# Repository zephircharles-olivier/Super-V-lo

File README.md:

C’est en combinant passion pour le cyclisme et intérêt pour les systèmes embarqués que j’ai imaginé le Super Vélo : un projet de fin d’année visant à transformer un vélo traditionnel en un moyen de transport intelligent, pratique et connecté.

Le Super Vélo, comme son nom l’indique, regroupe une série d’améliorations techniques soigneusement intégrées. Éclairage avant, feux de signalisation, et collecte de données en temps réel ne sont que quelques-unes des fonctionnalités que j’ai développées pour améliorer la sécurité et l’expérience utilisateur. Grâce à une connexion Internet, les données de vitesse et de fréquence cardiaque sont transmises sur une base de données et consultables directement sur un téléphone cellulaire.

Vous pouvez trouvez içi le code source, les schémas électroniques, les fichiers Gerbers et les fichiers de conception

Voir le projet sur mon site Web: https://tgemaisonneuve.com/wp-admin/post.php?post=1706&action=edit

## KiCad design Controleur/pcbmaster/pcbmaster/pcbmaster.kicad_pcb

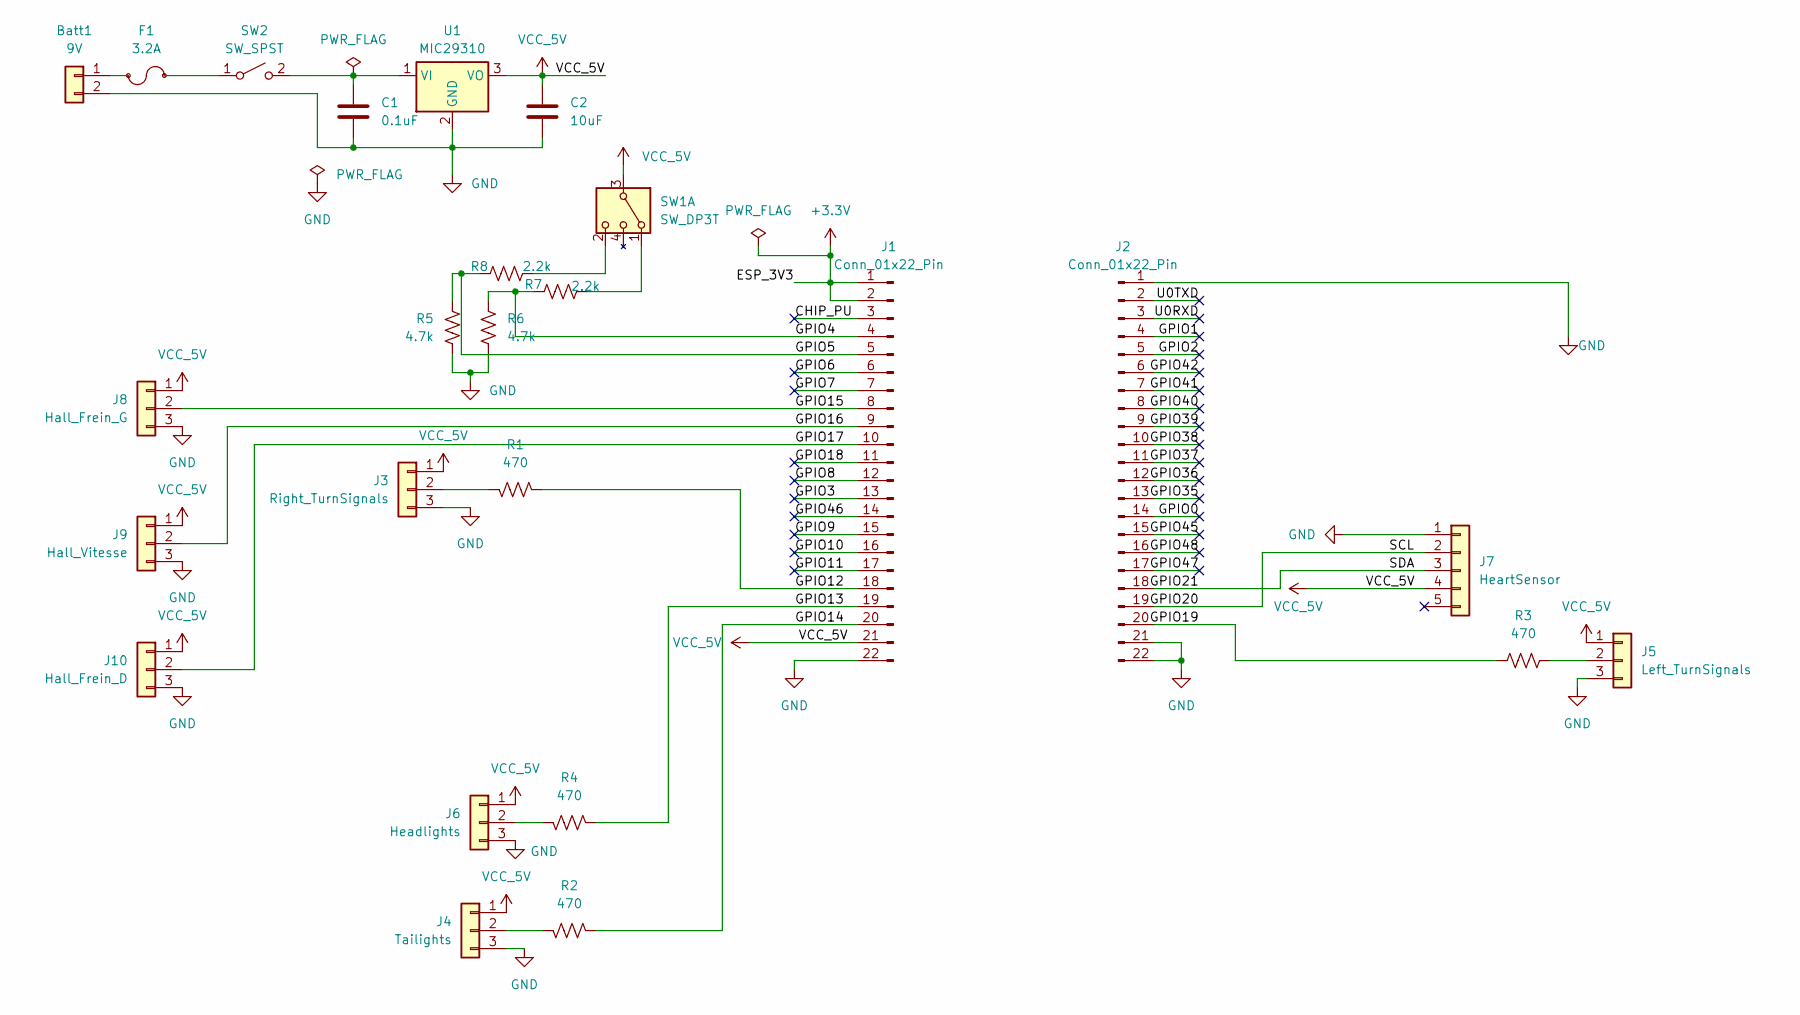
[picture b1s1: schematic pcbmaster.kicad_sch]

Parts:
Batt1: 9V; 691137710002
C1: 0.1uF; C_0805_2012Metric_Pad1.18x1.45mm_HandSolder
C2: 10uF; C_0805_2012Metric_Pad1.18x1.45mm_HandSolder
F1: 3.2A; FUSE_3519
J1, J2: Conn_01x22_Pin; PinHeader_1x22_P2.54mm_Vertical
J3: Right_TurnSignals; CONN_3pos_GREEN
J4: Tailights; CONN_3pos_GREEN
J5: Left_TurnSignals; CONN_3pos_GREEN
J6: Headlights; CONN_3pos_GREEN
J7: HeartSensor; CONN_5_pos_GREEN
J8: Hall_Frein_G; CONN_3pos_GREEN
J9: Hall_Vitesse; CONN_3pos_GREEN
J10: Hall_Frein_D; CONN_3pos_GREEN
R1, R2, R3, R4: 470; R_0805_2012Metric_Pad1.20x1.40mm_HandSolder
R5, R6: 4.7k; LED_0805_2012Metric_Pad1.15x1.40mm_HandSolder
R7, R8: 2.2k; LED_0805_2012Metric_Pad1.15x1.40mm_HandSolder
SW1: SW_DP3T; CONN_3pos_GREEN
SW2: SW_SPST; 691137710002
U1: MIC29310; TO-220-3_MCL

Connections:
+3.3V: J1.1, J1.2
/CHIP_PU: J1.3
/GPIO0: J2.14
/GPIO1: J2.4
/GPIO2: J2.5
/GPIO3: J1.13
/GPIO4: J1.4, R6.2, R7.1, R7.2, SW1.1 (IO1)
/GPIO5: J1.5, R5.2, R8.1, R8.2, SW1.2 (IO2)
/GPIO6: J1.6
/GPIO7: J1.7
/GPIO8: J1.12
/GPIO9: J1.15
/GPIO10: J1.16
/GPIO11: J1.17
/GPIO12: J1.18, R1.1
/GPIO13: J1.19, R4.1
/GPIO14: J1.20, R2.1
/GPIO15: J1.8, J8.2
/GPIO16: J1.9, J9.2
/GPIO17: J1.10, J10.2
/GPIO18: J1.11
/GPIO19: J2.20, R3.1
/GPIO20: J2.19, J7.2
/GPIO21: J2.18, J7.3
/GPIO35: J2.13
/GPIO36: J2.12
/GPIO37: J2.11
/GPIO38: J2.10
/GPIO39: J2.9
/GPIO40: J2.8
/GPIO41: J2.7
/GPIO42: J2.6
/GPIO45: J2.15
/GPIO46: J1.14
/GPIO47: J2.17
/GPIO48: J2.16
/U0RXD: J2.3
/U0TXD: J2.2
GND: Batt1.2, C1.2, C2.2, J1.22, J2.1, J2.21, J2.22, J3.3, J4.3, J5.3, J6.3, J7.1, J8.3, J9.3, J10.3, R5.1, R6.1, U1.2 (GND)
unnamed: Batt1.1, F1.1
unnamed: J3.2, R1.2
unnamed: J4.2, R2.2
unnamed: J5.2, R3.2
unnamed: J6.2, R4.2
unnamed: F1.2, SW2.1 (A)
unnamed: C1.1, SW2.2 (B), U1.1 (VI)
VCC_5V: C2.1, J1.21, J3.1, J4.1, J5.1, J6.1, J7.4, J8.1, J9.1, J10.1, SW1.3 (VCC), U1.3 (VO)

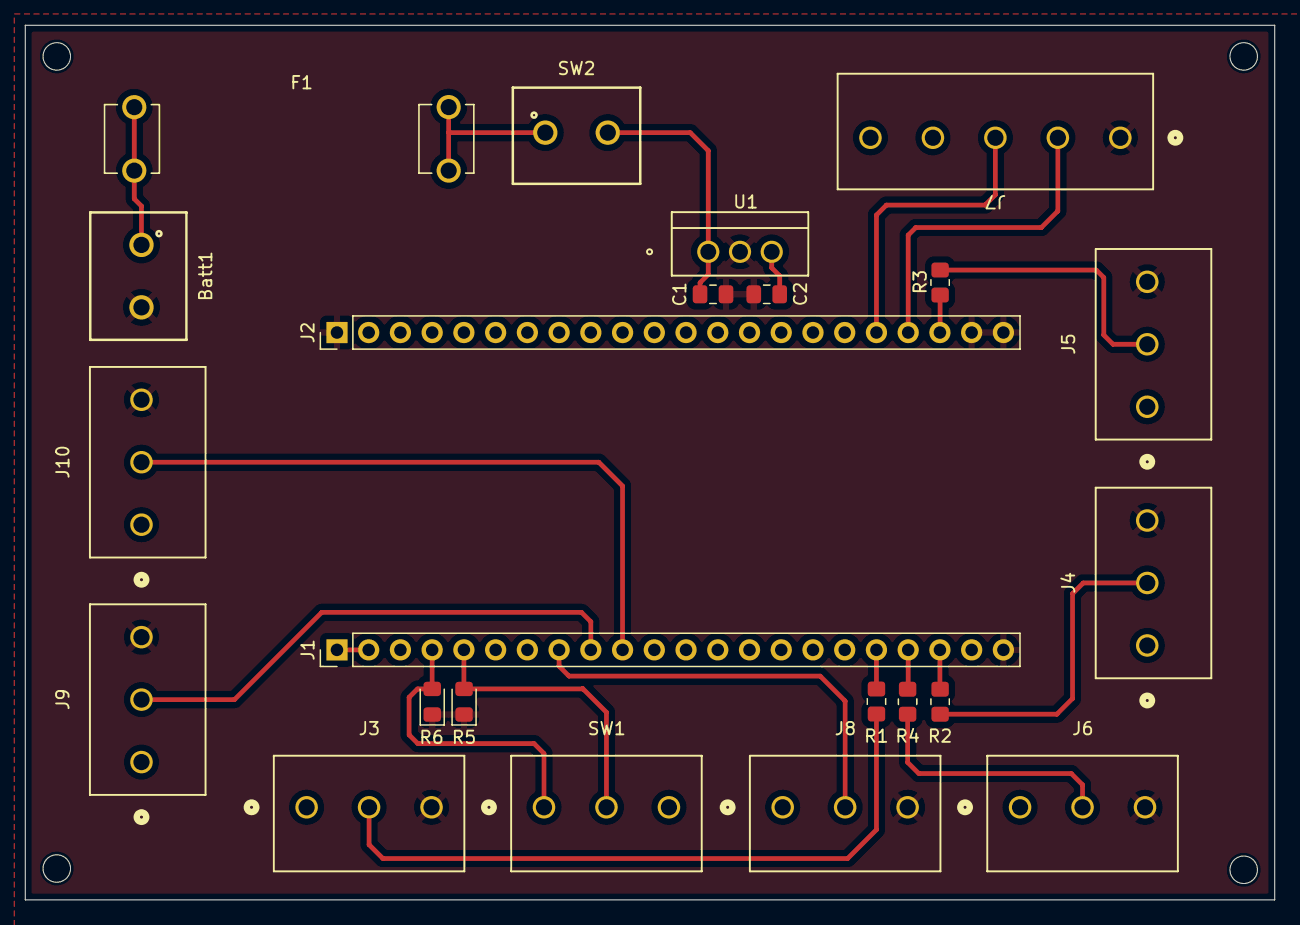
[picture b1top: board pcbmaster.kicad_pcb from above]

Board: 2 copper layers, 100.0 x 70.0 mm, 23 parts (0 on the bottom side), 21 nets.

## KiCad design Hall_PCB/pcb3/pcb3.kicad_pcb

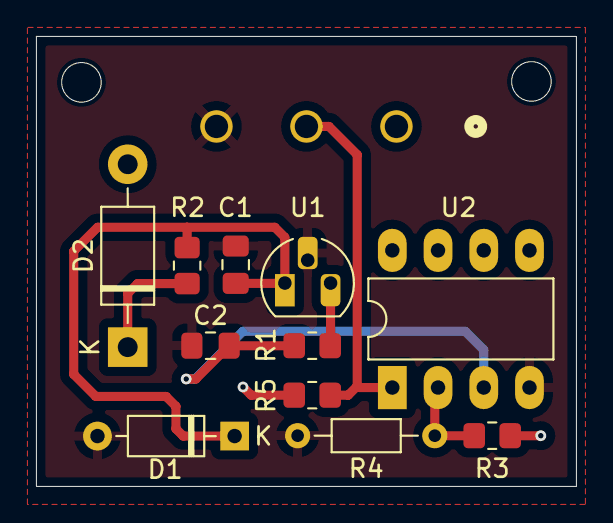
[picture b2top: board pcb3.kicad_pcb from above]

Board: 2 copper layers, 30.0 x 25.0 mm, 12 parts (1 on the bottom side), 8 nets.

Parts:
C1: 100nF; C_0805_2012Metric_Pad1.18x1.45mm_HandSolder
C2: 4.7nF; C_0805_2012Metric_Pad1.18x1.45mm_HandSolder
D1: D_Zener; D_DO-35_SOD27_P7.62mm_Horizontal
D2: 1N4004-TP; D_DO-41_SOD81_P10.16mm_Horizontal
J1: Hall_Vitesse; CONN_3pos_GREEN
R1, R3, R5: 10k; R_0805_2012Metric_Pad1.20x1.40mm_HandSolder
R2: 100; R_0805_2012Metric_Pad1.20x1.40mm_HandSolder
R4: 500; R_Axial_DIN0204_L3.6mm_D1.6mm_P7.62mm_Horizontal
U1: US5881; TO-92L_HandSolder
U2: LM393; DIP-8_W7.62mm_LongPads

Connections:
+5V: D2.2 (A), J1.1, R3.1, R5.1, U2.8 (V+)
/OUT_5V: J1.2, R5.2, U2.1
GND: C1.2, C2.1, D1.2 (A), J1.3, R4.2, U1.2 (GND), U2.4 (V-)
unnamed: C1.1, D1.1 (K), R2.2, U1.1 (VDD)
unnamed: D2.1 (K), R2.1
unnamed: R1.1, U1.3 (OUT)
unnamed: C2.2, R1.2, U2.3 (+)
unnamed: R3.2, R4.1, U2.2 (-)

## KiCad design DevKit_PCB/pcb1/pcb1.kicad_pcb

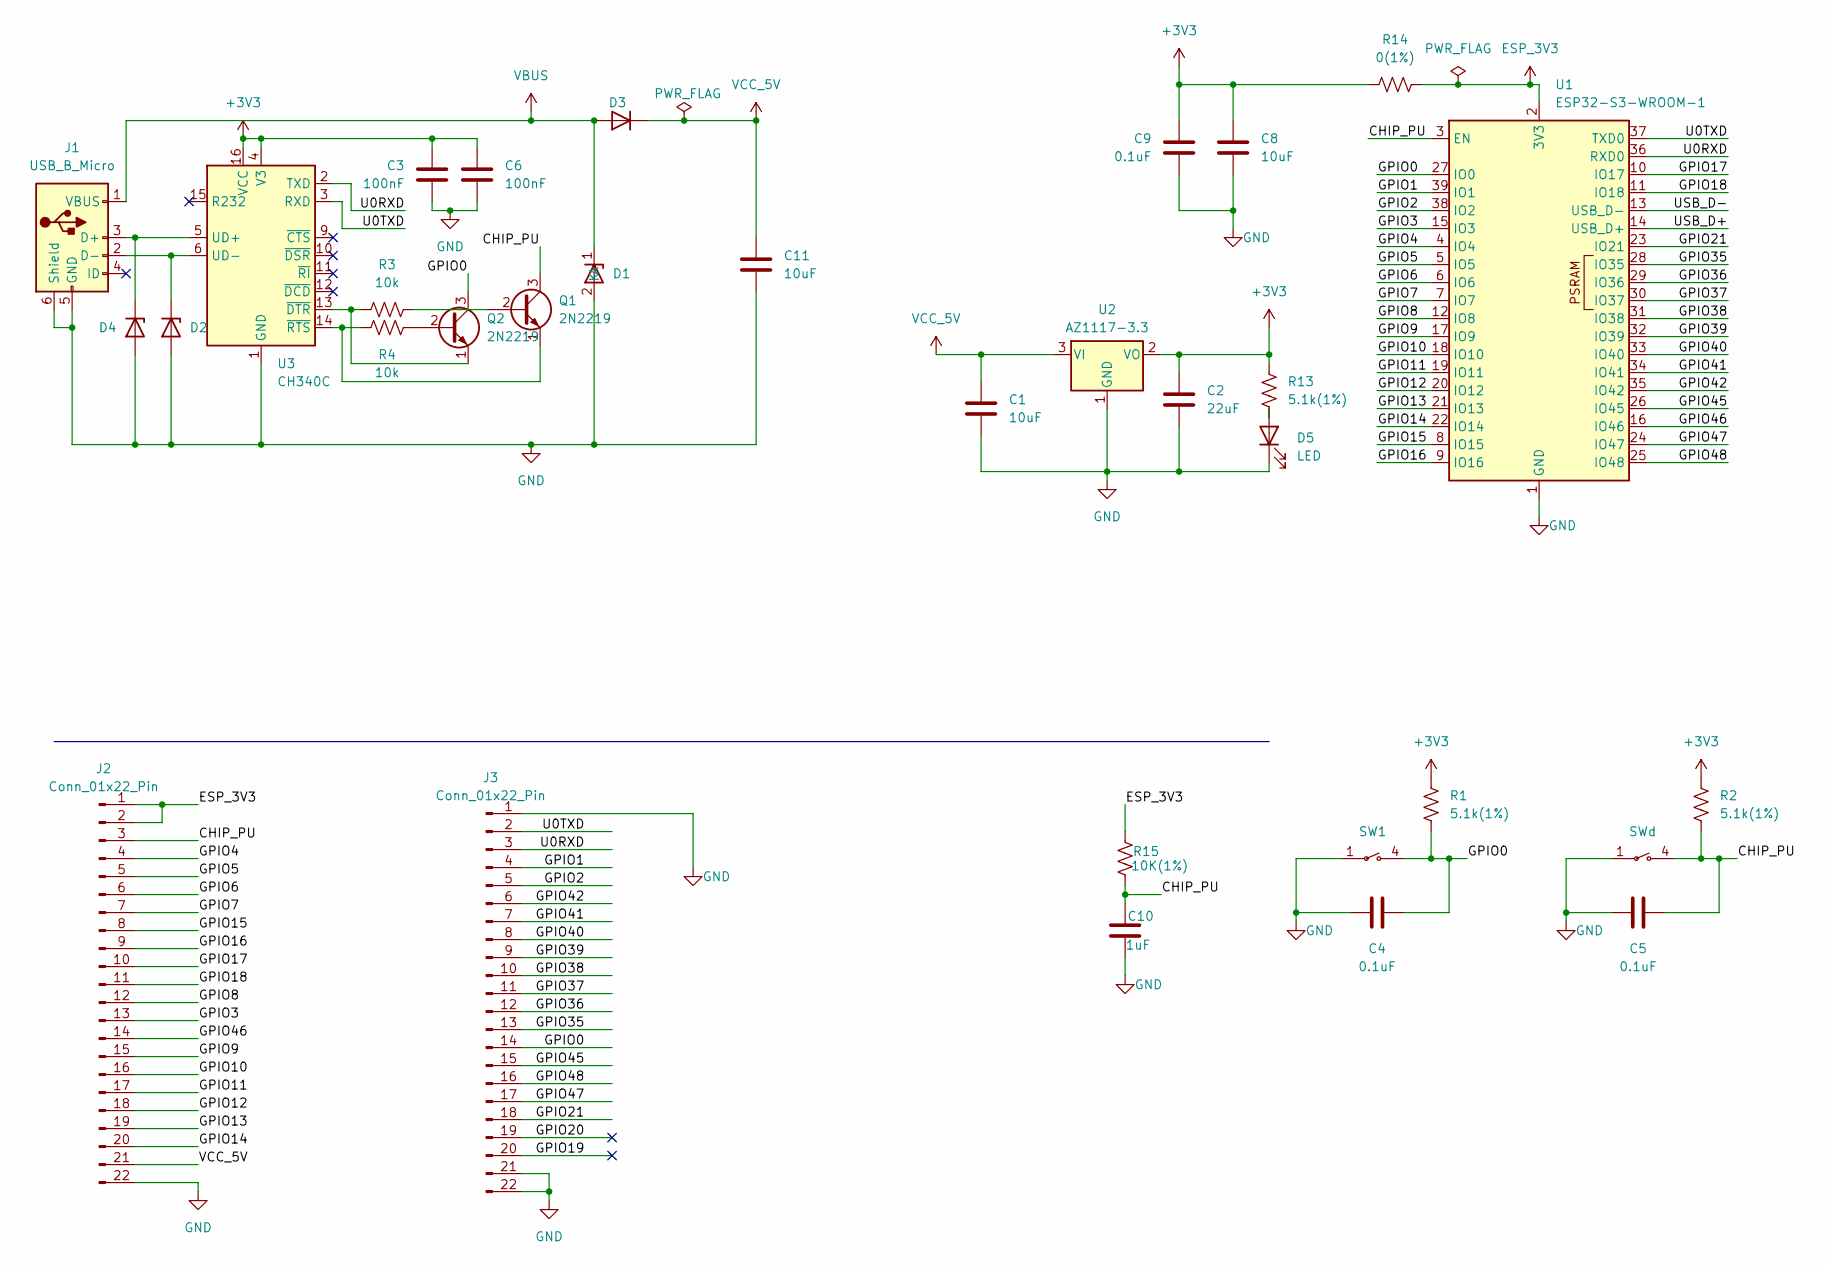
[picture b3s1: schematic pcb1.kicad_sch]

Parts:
C1, C11: 10uF; C_10uF
C2: 22uF; C_size0805
C3, C6: 100nF; C_size0805
C4, C5, C9: 0.1uF; C_0805_2012Metric
C8: 10uF; C_size0805
C10: 1uF; C_0805_2012Metric
D1, D2, D4: SMA6J58CA-Q; CR_041-1JY_STM
D3: Schottky
D5: LED; LED_R
J1: USB_B_Micro; USB2.0(10118193)
J2, J3: Conn_01x22_Pin; PinHeader_1x22_P2.54mm_Vertical
Q1, Q2: 2N2219; BSR14
R1, R2, R13: 5.1k(1%); R_0805_2012Metric
R3, R4: 10k; R_10k(1%)
R14: 0(1%); R_0
R15: 10K(1%); R_10k(1%)
SW1: PTS 647 SN50 SMTR2 LFS
SWd: PTS 647 SN50 SMTR2 LFS
U1: ESP32-S3-WROOM-1
U2: AZ1117-3.3; SOT-223-3_TabPin2
U3: CH340C; SOIC-16_3.9x9.9mm_P1.27mm

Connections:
+3V3: C2.1, C3.1, C6.1, C8.1, C9.1, R1.2, R2.2, R13.2, R14.1, U2.2 (VO), U3.4 (V3), U3.16 (VCC)
/CHIP_PU: C5.2, C10.1, J2.3, Q1.3 (C), R2.1, R15.2, SWd.4, U1.3 (EN); also elsewhere on the board
/GPIO0: C4.2, J3.14, Q2.3 (C), R1.1, SW1.4, U1.27 (IO0)
/GPIO1: J3.4, U1.39 (IO1)
/GPIO2: J3.5, U1.38 (IO2)
/GPIO3: J2.13, U1.15 (IO3)
/GPIO4: J2.4, U1.4 (IO4)
/GPIO5: J2.5, U1.5 (IO5)
/GPIO6: J2.6, U1.6 (IO6)
/GPIO7: J2.7, U1.7 (IO7)
/GPIO8: J2.12, U1.12 (IO8)
/GPIO9: J2.15, U1.17 (IO9)
/GPIO10: J2.16, U1.18 (IO10)
/GPIO11: J2.17, U1.19 (IO11)
/GPIO12: J2.18, U1.20 (IO12)
/GPIO13: J2.19, U1.21 (IO13)
/GPIO14: J2.20, U1.22 (IO14)
/GPIO15: J2.8, U1.8 (IO15)
/GPIO16: J2.9, U1.9 (IO16)
/GPIO17: J2.10, U1.10 (IO17)
/GPIO18: J2.11, U1.11 (IO18)
/GPIO19: J3.20
/GPIO20: J3.19
/GPIO21: J3.18, U1.23 (IO21)
/GPIO35: J3.13, U1.28 (IO35)
/GPIO36: J3.12, U1.29 (IO36)
/GPIO37: J3.11, U1.30 (IO37)
/GPIO38: J3.10, U1.31 (IO38)
/GPIO39: J3.9, U1.32 (IO39)
/GPIO40: J3.8, U1.33 (IO40)
/GPIO41: J3.7, U1.34 (IO41)
/GPIO42: J3.6, U1.35 (IO42)
/GPIO45: J3.15, U1.26 (IO45)
/GPIO46: J2.14, U1.16 (IO46)
/GPIO47: J3.17, U1.24 (IO47)
/GPIO48: J3.16, U1.25 (IO48)
/U0RXD: J3.3, U1.36 (RXD0), U3.2 (TXD)
/U0TXD: J3.2, U1.37 (TXD0), U3.3 (RXD)
/USB_D+: U1.14 (USB_D+)
/USB_D-: U1.13 (USB_D-)
ESP_3V3: J2.1, J2.2, R14.2, R15.1, U1.2 (3V3)
GND: C1.2, C2.2, C3.2, C4.1, C5.1, C6.2, C8.2, C9.2, C10.2, C11.2, D1.2 (A), D2.2 (A), D4.2 (A), D5.1 (K), J1.5 (GND), J1.6 (Shield), J2.22, J3.1, J3.21, J3.22, SW1.1, SWd.1, U1.1 (GND), U1.40 (GND), U1.41 (GND), U2.1 (GND), U3.1 (GND); also elsewhere on the board
unnamed: D2.1 (K), J1.2 (D-), U3.6 (UD-)
unnamed: D4.1 (K), J1.3 (D+), U3.5 (UD+)
unnamed: D5.2 (A), R13.1
unnamed: Q1.2 (B), R3.2
unnamed: Q1.1 (E), R4.1, U3.14 (~RTS)
unnamed: Q2.2 (B), R4.2
unnamed: Q2.1 (E), R3.1, U3.13 (~DTR)
VBUS: D1.1 (K), D3.2 (A), J1.1 (VBUS)
VCC_5V: C1.1, C11.1, D3.1 (K), J2.21, U2.3 (VI)

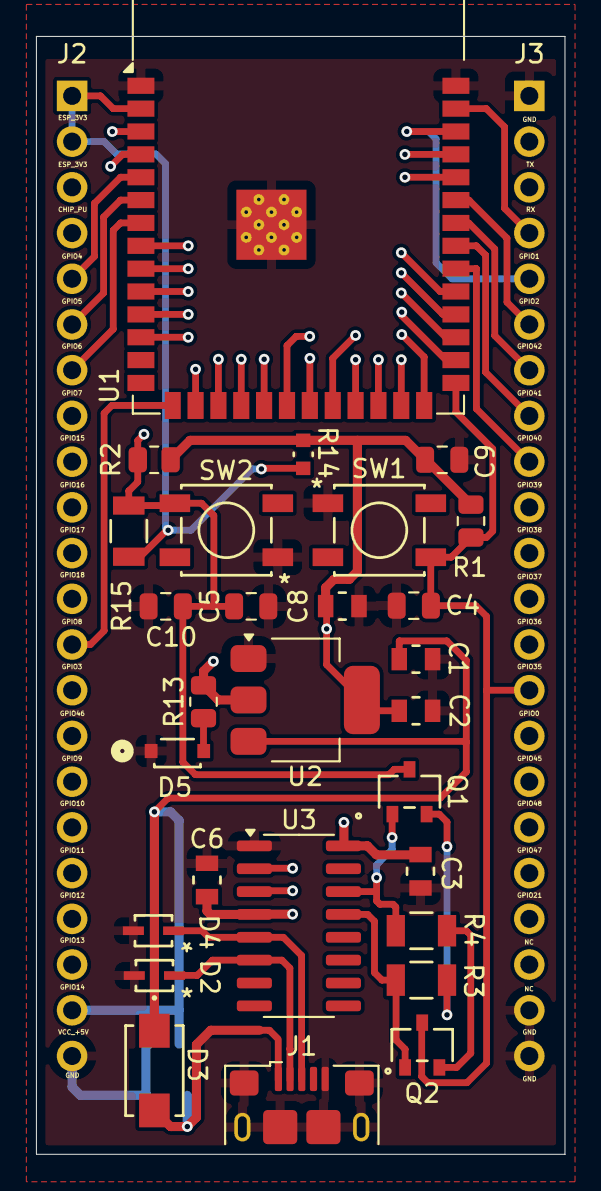
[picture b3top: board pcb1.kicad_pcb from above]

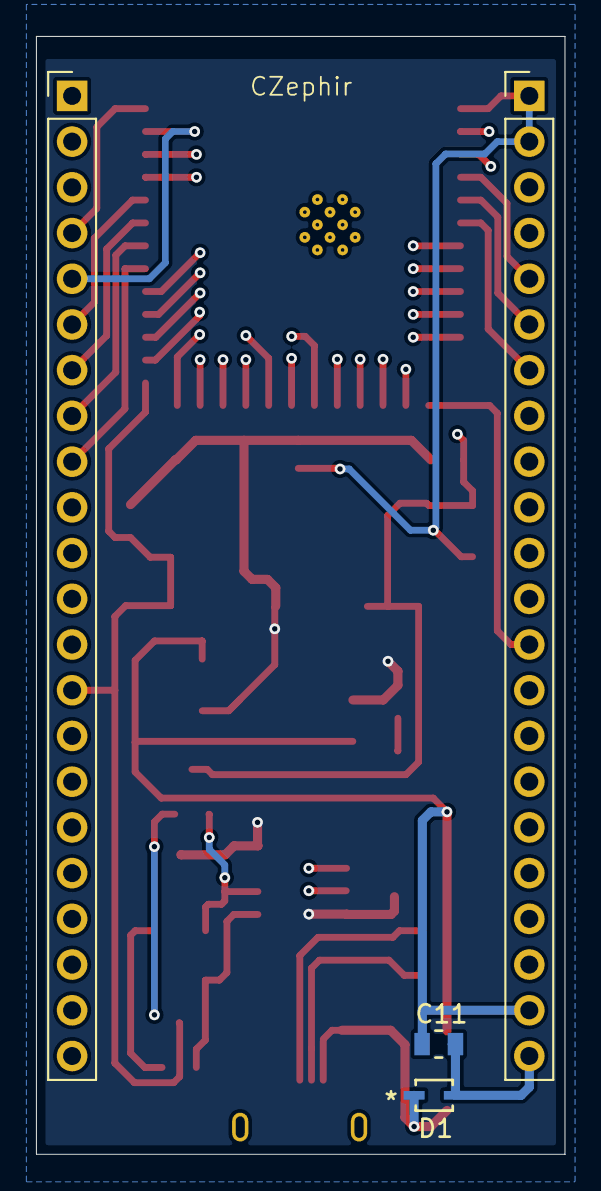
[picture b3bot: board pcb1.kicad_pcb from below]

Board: 4 copper layers, 29.4 x 62.1 mm, 32 parts (4 on the bottom side), 47 nets.

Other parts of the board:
SW2: PTS 647 SN50 SMTR2 LFS

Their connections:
/CHIP_PU: SW2.4; also elsewhere on the board
GND: SW2.1; also elsewhere on the board

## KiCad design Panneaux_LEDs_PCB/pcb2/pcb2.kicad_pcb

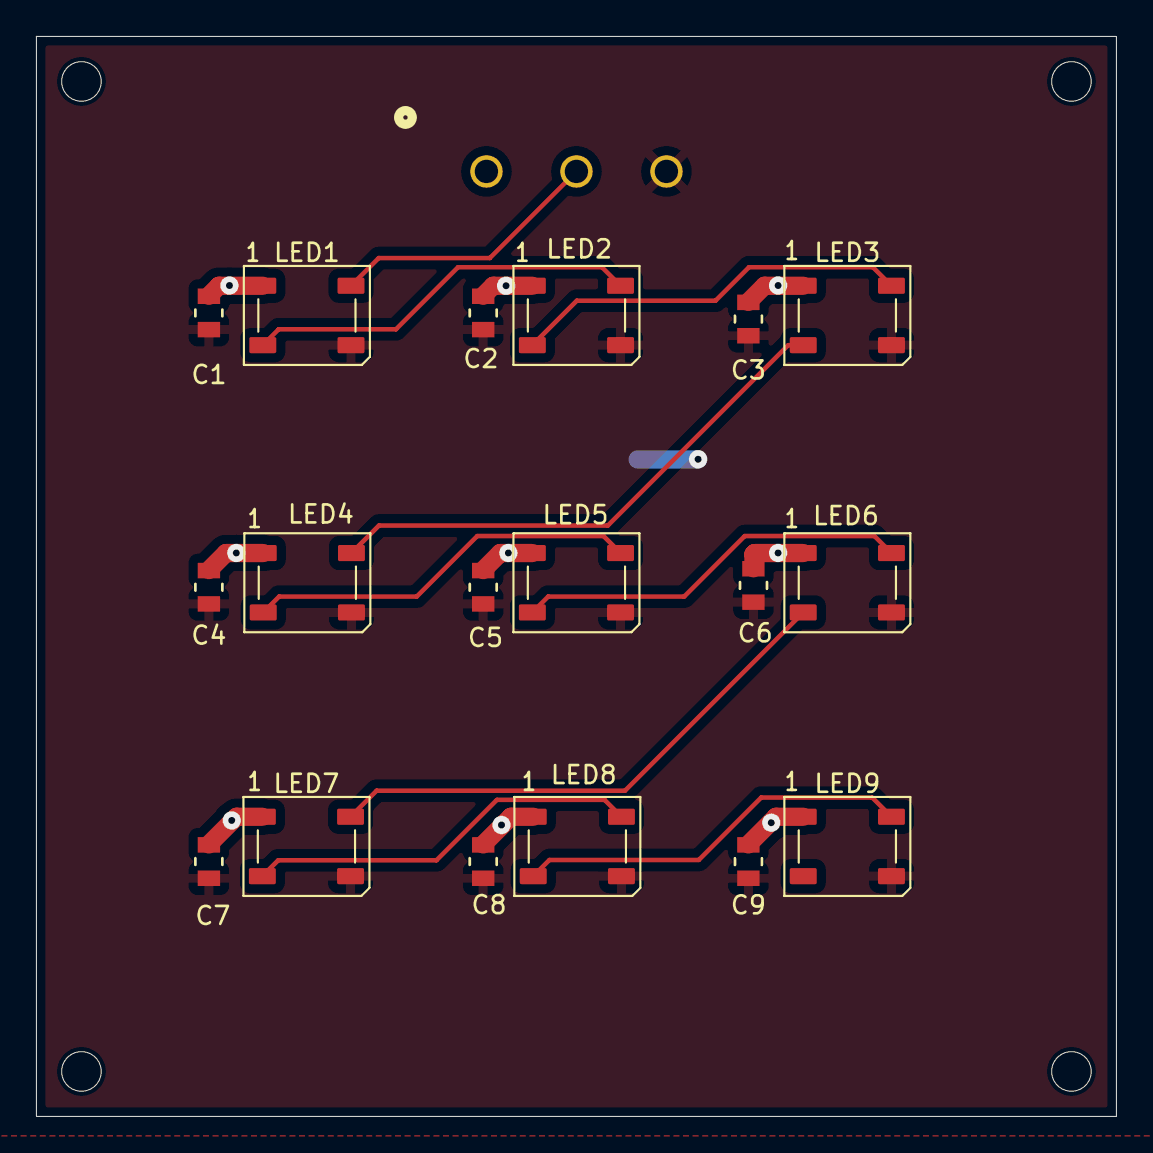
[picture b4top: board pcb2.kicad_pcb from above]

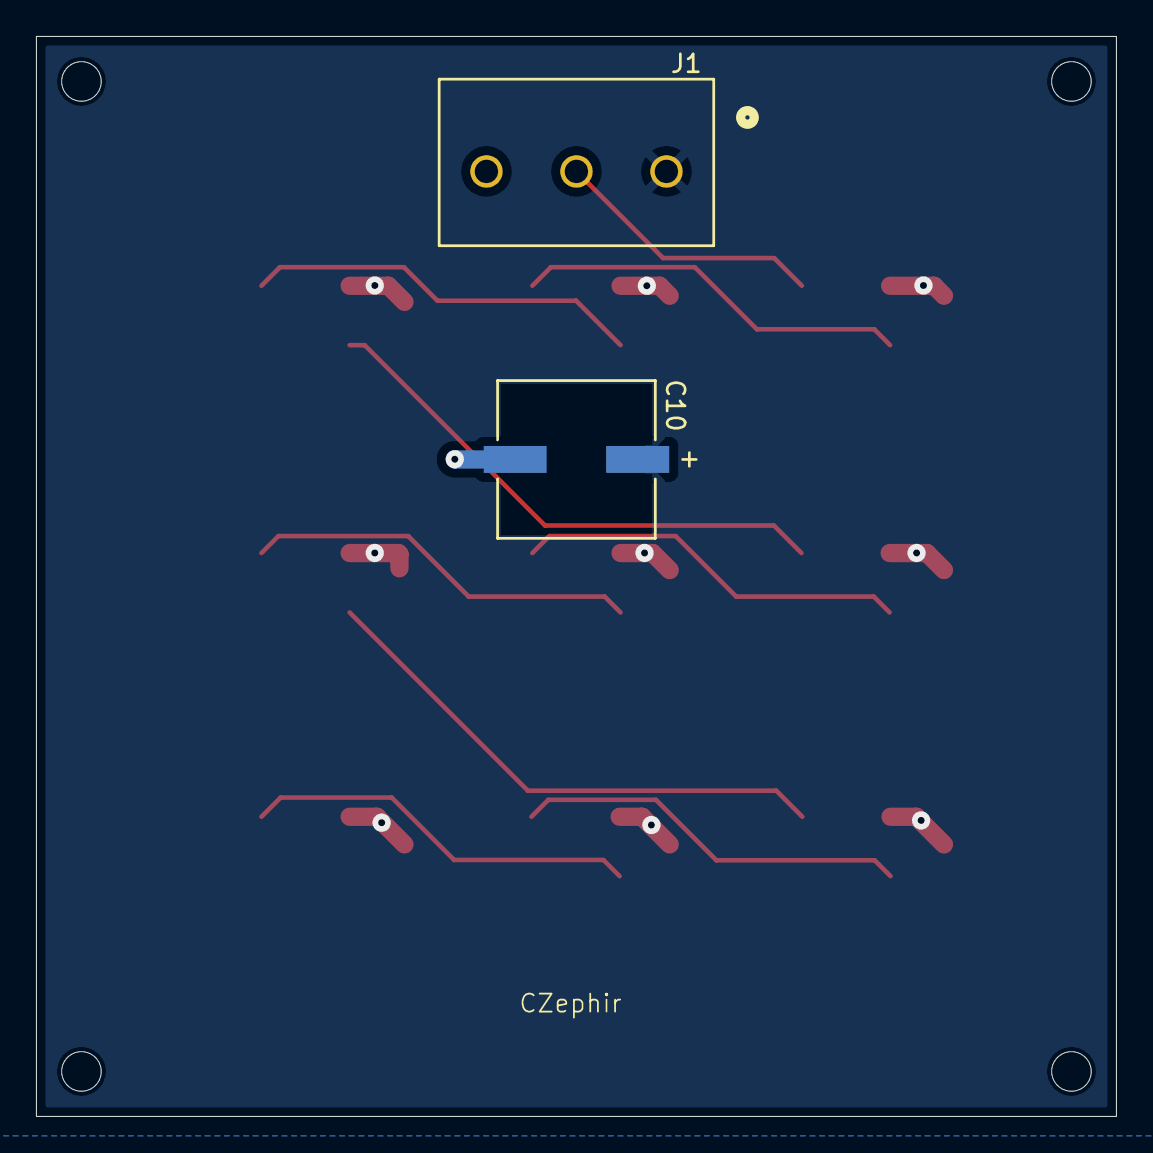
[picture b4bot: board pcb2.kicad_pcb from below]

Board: 2 copper layers, 60.0 x 60.0 mm, 20 parts (2 on the bottom side), 11 nets.

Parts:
C1, C2, C3, C4, C5, C6, C7, C8, C9: 0.1uF; C_size0805
C10: 470uF; PCAP_8x10-ELECT_NCA
J1: Lumière; CONN_3pos_GREEN
LED1, LED2, LED3, LED4, LED5, LED6, LED7, LED8, LED9: LED_WS2812B_PLCC4_5.0x5.0mm_P3.2mm

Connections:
+5V: C1.1, C2.1, C3.1, C4.1, C5.1, C6.1, C7.1, C8.1, C9.1, C10.1, J1.1, LED1.1 (VDD), LED2.1 (VDD), LED3.1 (VDD), LED4.1 (VDD), LED5.1 (VDD), LED6.1 (VDD), LED7.1 (VDD), LED8.1 (VDD), LED9.1 (VDD)
GND: C1.2, C2.2, C3.2, C4.2, C5.2, C6.2, C7.2, C8.2, C9.2, C10.2, J1.3, LED1.3 (VSS), LED2.3 (VSS), LED3.3 (VSS), LED4.3 (VSS), LED5.3 (VSS), LED6.3 (VSS), LED7.3 (VSS), LED8.3 (VSS), LED9.3 (VSS)
unnamed: J1.2, LED1.4 (DIN)
unnamed: LED1.2 (DOUT), LED2.4 (DIN)
unnamed: LED2.2 (DOUT), LED3.4 (DIN)
unnamed: LED3.2 (DOUT), LED4.4 (DIN)
unnamed: LED4.2 (DOUT), LED5.4 (DIN)
unnamed: LED5.2 (DOUT), LED6.4 (DIN)
unnamed: LED6.2 (DOUT), LED7.4 (DIN)
unnamed: LED7.2 (DOUT), LED8.4 (DIN)
unnamed: LED8.2 (DOUT), LED9.4 (DIN)

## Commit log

2025-05-16 controleur et firemware
